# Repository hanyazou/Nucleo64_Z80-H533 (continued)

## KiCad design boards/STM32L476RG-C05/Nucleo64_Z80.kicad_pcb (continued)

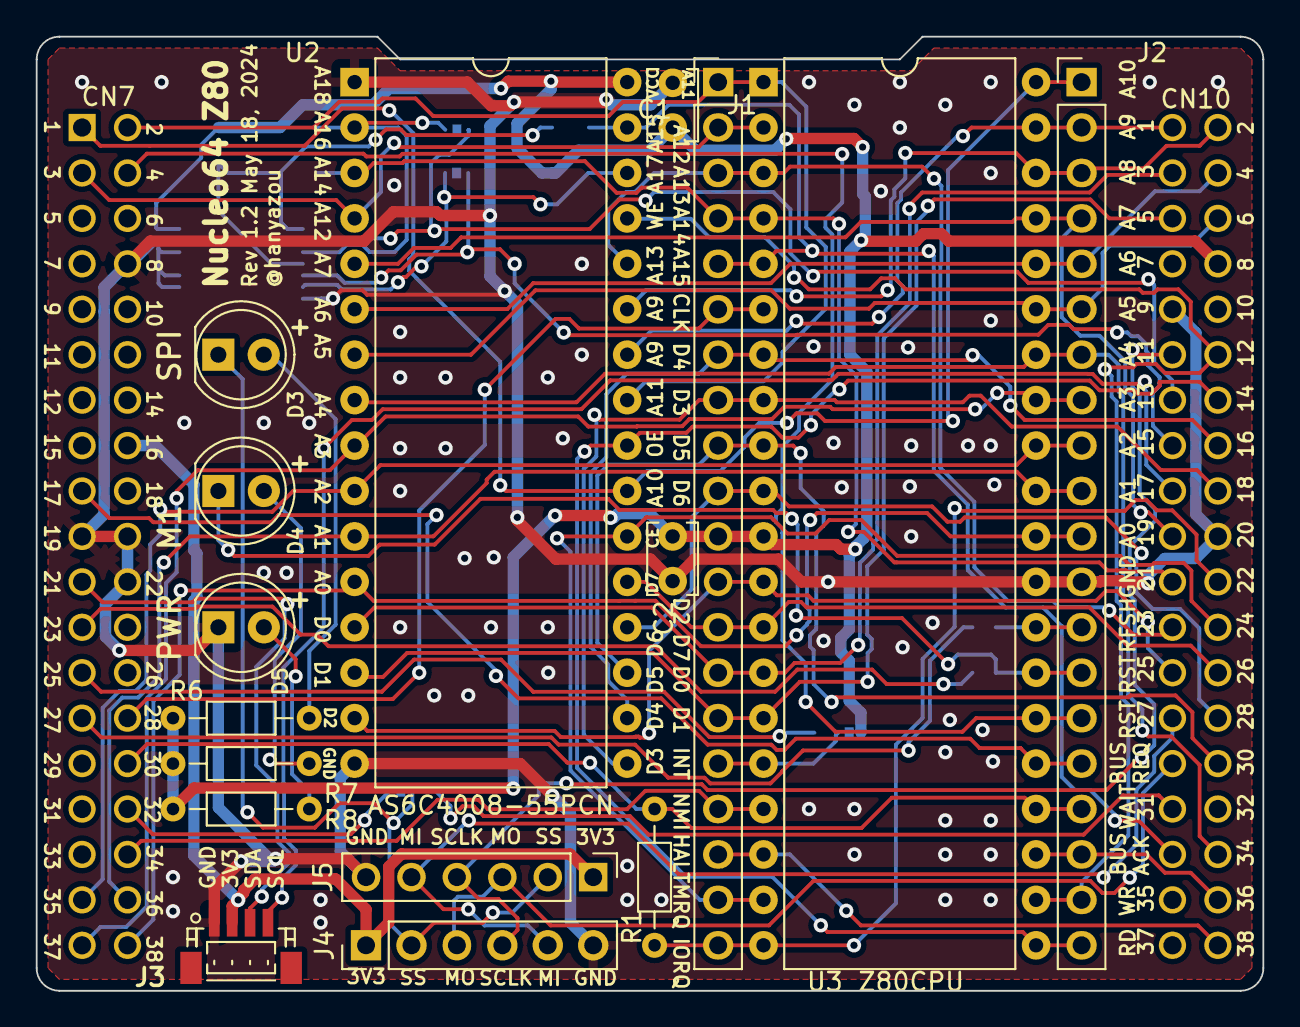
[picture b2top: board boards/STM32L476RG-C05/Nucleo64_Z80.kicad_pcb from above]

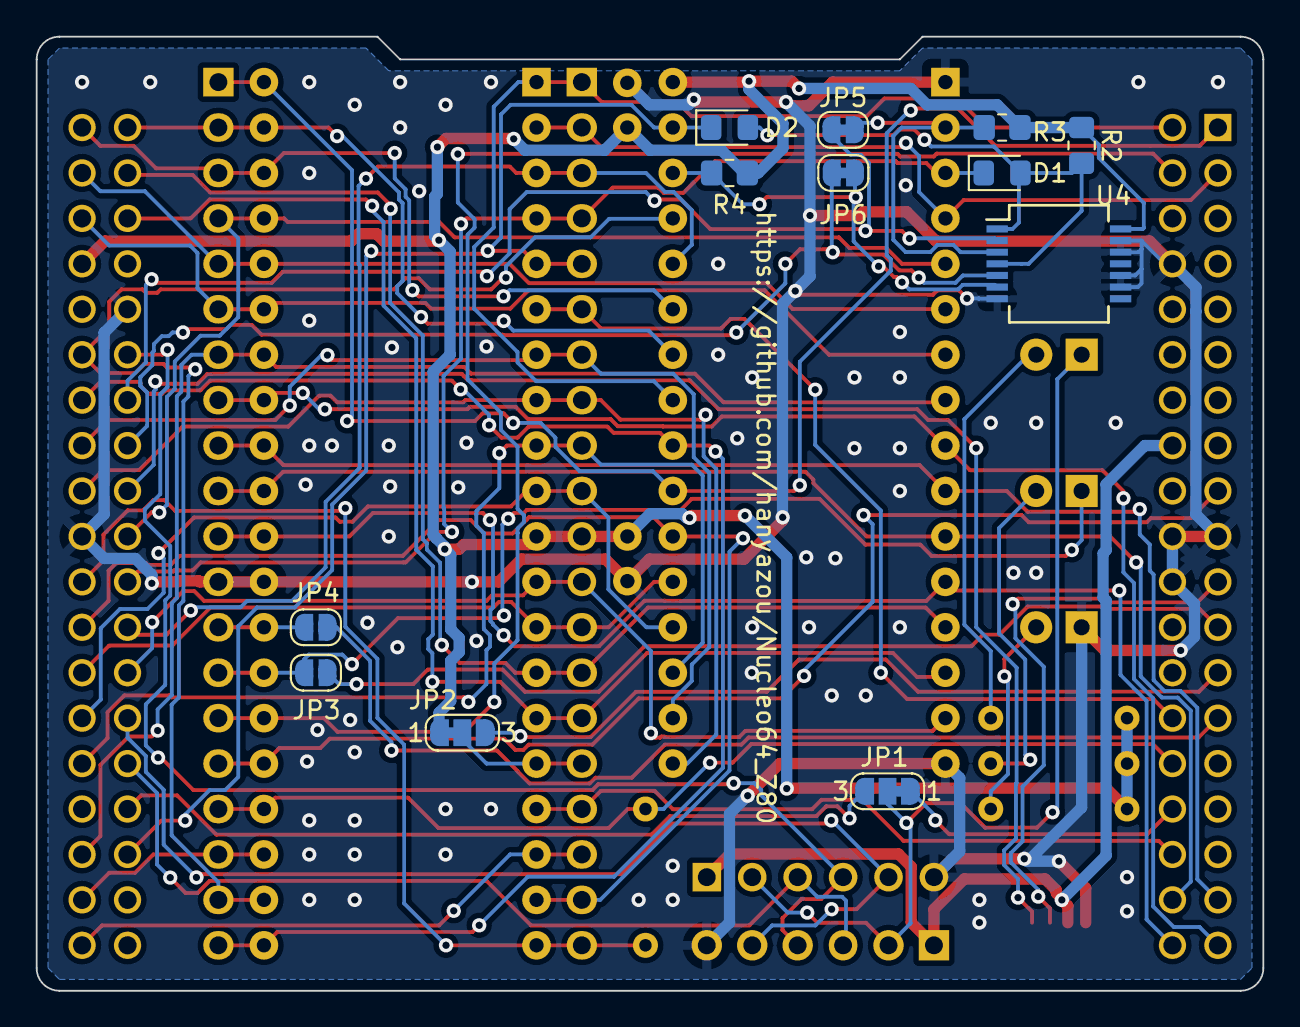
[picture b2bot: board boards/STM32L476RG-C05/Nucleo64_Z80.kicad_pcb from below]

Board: 2 copper layers, 68.6 x 53.3 mm, 29 parts (12 on the bottom side), 60 nets.

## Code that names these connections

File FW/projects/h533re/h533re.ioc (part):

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Mcu.Name=STM32H533RETx
Mcu.Package=LQFP64
Mcu.UserName=STM32H533RETx
PA0.Signal=S_TIM2_CH1
PA1.GPIOParameters=GPIO_Label
PA1.GPIO_Label=Z80_IOREQ
PA1.Signal=GPIO_Input
PA10.GPIOParameters=GPIO_Label
PA10.GPIO_Label=Z80_PWR_EN
PA10.Signal=GPIO_Output
PA11.Mode=Host
PA11.Signal=USB_DM
PA12.Mode=Host
PA12.Signal=USB_DP
PA15(JTDI).GPIOParameters=GPIO_Label
PA15(JTDI).GPIO_Label=Z80_NMI
PA15(JTDI).Signal=GPIO_Input
PA2.Mode=Asynchronous
PA2.Signal=USART2_TX
PA3.Mode=Asynchronous
PA3.Signal=USART2_RX
PA4.GPIOParameters=GPIO_Label
PA4.GPIO_Label=USB_FS_PWR_EN
PA4.Signal=GPIO_Output
PA5.GPIOParameters=GPIO_Label
PA5.GPIO_Label=BANK_SEL0
PA5.Mode=Full_Duplex_Master
PA5.Signal=SPI1_SCK
PA6.GPIOParameters=GPIO_Label
PA6.GPIO_Label=BANK_SEL1
PA6.Mode=Full_Duplex_Master
PA6.Signal=SPI1_MISO
PA7.GPIOParameters=GPIO_Label
PA7.GPIO_Label=Z80_INT
PA7.Mode=Full_Duplex_Master
PA7.Signal=SPI1_MOSI
PA8.GPIOParameters=GPIO_Label
PA8.GPIO_Label=Z80_WAIT
PA8.Signal=GPIO_Input
PA9.GPIOParameters=PinState,GPIO_Label
PA9.GPIO_Label=SPI_SS
PA9.PinState=GPIO_PIN_SET
PA9.Signal=GPIO_Output
PB0.GPIOParameters=GPIO_Label
PB0.GPIO_Label=Z80_D0
PB0.Signal=GPIO_Input
PB1.GPIOParameters=GPIO_Label
PB1.GPIO_Label=Z80_D1
PB1.Signal=GPIO_Input
PB10.Mode=I2C
PB10.Signal=I2C2_SCL
PB12.Mode=I2C
PB12.Signal=I2C2_SDA
PB13.GPIOParameters=GPIO_Label
PB13.GPIO_Label=Z80_A13
PB13.Signal=GPIO_Input
PB14.GPIOParameters=GPIO_Label
PB14.GPIO_Label=Z80_A14
PB14.Signal=GPIO_Input
PB15.GPIOParameters=GPIO_Label
PB15.GPIO_Label=Z80_A15
PB15.Signal=GPIO_Input
PB2.GPIOParameters=GPIO_Label
PB2.GPIO_Label=Z80_D2
PB2.Signal=GPIO_Input
PB3(JTDO/TRACESWO).GPIOParameters=GPIO_Label
PB3(JTDO/TRACESWO).GPIO_Label=Z80_D3
PB3(JTDO/TRACESWO).Signal=GPIO_Input
PB4(NJTRST).GPIOParameters=GPIO_Label
PB4(NJTRST).GPIO_Label=Z80_D4
PB4(NJTRST).Signal=GPIO_Input
PB5.GPIOParameters=GPIO_Label
PB5.GPIO_Label=Z80_D5
PB5.Signal=GPIO_Input
PB6.GPIOParameters=GPIO_Label
PB6.GPIO_Label=Z80_D6
PB6.Signal=GPIO_Input
PB7.GPIOParameters=GPIO_Label
PB7.GPIO_Label=Z80_D7
PB7.Signal=GPIO_Input
PB8.GPIOParameters=GPIO_Label
PB8.GPIO_Label=Z80_RD
PB8.Signal=GPIO_Input
PC0.GPIOParameters=GPIO_Label
PC0.GPIO_Label=Z80_A0
PC0.Signal=GPIO_Input
PC1.GPIOParameters=GPIO_Label
PC1.GPIO_Label=Z80_A1
PC1.Signal=GPIO_Input
PC10.GPIOParameters=GPIO_Label
PC10.GPIO_Label=Z80_A10
PC10.Signal=GPIO_Input
PC11.GPIOParameters=GPIO_Label
PC11.GPIO_Label=Z80_A11
PC11.Signal=GPIO_Input
PC12.GPIOParameters=GPIO_Label
PC12.GPIO_Label=Z80_A12
PC12.Signal=GPIO_Input
PC13.GPIOParameters=GPIO_Label
PC13.GPIO_Label=Z80_RESET
PC13.Signal=GPIO_Input
PC14-OSC32_IN(OSC32_IN).GPIOParameters=GPIO_Label
PC14-OSC32_IN(OSC32_IN).GPIO_Label=Z80_MEMRQ
PC14-OSC32_IN(OSC32_IN).Signal=GPIO_Input
PC15-OSC32_OUT(OSC32_OUT).GPIOParameters=GPIO_Label
PC15-OSC32_OUT(OSC32_OUT).GPIO_Label=Z80_WR
PC15-OSC32_OUT(OSC32_OUT).Signal=GPIO_Input
PC2.GPIOParameters=GPIO_Label
PC2.GPIO_Label=Z80_A2
PC2.Signal=GPIO_Input
PC3.GPIOParameters=GPIO_Label
PC3.GPIO_Label=Z80_A3
PC3.Signal=GPIO_Input
PC4.GPIOParameters=GPIO_Label
PC4.GPIO_Label=Z80_A4
PC4.Signal=GPIO_Input
PC5.GPIOParameters=GPIO_Label
PC5.GPIO_Label=Z80_A5
PC5.Signal=GPIO_Input
PC6.GPIOParameters=GPIO_Label
PC6.GPIO_Label=Z80_A6
PC6.Signal=GPIO_Input
PC7.GPIOParameters=GPIO_Label
PC7.GPIO_Label=Z80_A7
PC7.Signal=GPIO_Input
PC8.GPIOParameters=GPIO_Label
PC8.GPIO_Label=Z80_A8
PC8.Signal=GPIO_Input
PC9.GPIOParameters=GPIO_Label
PC9.GPIO_Label=Z80_A9
PC9.Signal=GPIO_Input
PD2.GPIOParameters=GPIO_Label
PD2.GPIO_Label=Z80_BUSRQ
PD2.Signal=GPIO_Input
RCC.HSE_VALUE=25000000
RCC.SYSCLKFreq_VALUE=248000000
RCC.SYSCLKSource=RCC_SYSCLKSOURCE_PLLCLK
board=custom

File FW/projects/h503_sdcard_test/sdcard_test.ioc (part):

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Mcu.Name=STM32L476R(C-E-G)Tx
Mcu.Package=LQFP64
Mcu.UserName=STM32L476RGTx
PA0.Signal=S_TIM5_CH1
PA1.GPIOParameters=GPIO_PuPd,GPIO_Label
PA1.GPIO_Label=Z80_WAIT
PA1.GPIO_PuPd=GPIO_PULLUP
PA1.Signal=GPIO_Input
PA10.GPIOParameters=GPIO_PuPd,GPIO_Label
PA10.GPIO_Label=Z80_A15
PA10.GPIO_PuPd=GPIO_NOPULL
PA10.Signal=GPIO_Input
PA11.GPIOParameters=GPIO_PuPd,GPIO_Label
PA11.GPIO_Label=Z80_RD
PA11.GPIO_PuPd=GPIO_PULLUP
PA11.Signal=GPIO_Input
PA12.GPIOParameters=GPIO_PuPd,GPIO_Label
PA12.GPIO_Label=Z80_WR
PA12.GPIO_PuPd=GPIO_PULLUP
PA12.Signal=GPIO_Input
PA13\ (JTMS-SWDIO).GPIOParameters=GPIO_Label
PA13\ (JTMS-SWDIO).GPIO_Label=TMS
PA13\ (JTMS-SWDIO).Mode=Serial_Wire
PA13\ (JTMS-SWDIO).Signal=SYS_JTMS-SWDIO
PA14\ (JTCK-SWCLK).GPIOParameters=GPIO_Label
PA14\ (JTCK-SWCLK).GPIO_Label=TCK
PA14\ (JTCK-SWCLK).Mode=Serial_Wire
PA14\ (JTCK-SWCLK).Signal=SYS_JTCK-SWCLK
PA15\ (JTDI).GPIOParameters=GPIO_Label
PA15\ (JTDI).GPIO_Label=Z80_BUSRQ
PA15\ (JTDI).Signal=GPIO_Output
PA2.GPIOParameters=GPIO_Speed,GPIO_PuPd,GPIO_Label,GPIO_Mode
PA2.GPIO_Label=USART_TX
PA2.GPIO_Mode=GPIO_MODE_AF_PP
PA2.GPIO_PuPd=GPIO_NOPULL
PA2.GPIO_Speed=GPIO_SPEED_FREQ_VERY_HIGH
PA2.Mode=Asynchronous
PA2.Signal=USART2_TX
PA3.GPIOParameters=GPIO_Speed,GPIO_PuPd,GPIO_Label,GPIO_Mode
PA3.GPIO_Label=USART_RX
PA3.GPIO_Mode=GPIO_MODE_AF_PP
PA3.GPIO_PuPd=GPIO_NOPULL
PA3.GPIO_Speed=GPIO_SPEED_FREQ_VERY_HIGH
PA3.Mode=Asynchronous
PA3.Signal=USART2_RX
PA4.GPIOParameters=PinState,GPIO_Label
PA4.GPIO_Label=SPI1_SS
PA4.PinState=GPIO_PIN_SET
PA4.Signal=GPIO_Output
PA5.Mode=Full_Duplex_Master
PA5.Signal=SPI1_SCK
PA6.GPIOParameters=GPIO_Label
PA6.GPIO_Label=BANK_SEL0
PA6.Signal=GPIO_Output
PA7.GPIOParameters=GPIO_Label
PA7.GPIO_Label=BANK_SEL1
PA7.Signal=GPIO_Output
PA8.GPIOParameters=GPIO_Label
PA8.GPIO_Label=Z80_A13
PA8.Signal=GPIO_Input
PA9.GPIOParameters=GPIO_Label
PA9.GPIO_Label=Z80_A14
PA9.Signal=GPIO_Input
PB0.GPIOParameters=GPIO_Label
PB0.GPIO_Label=Z80_NMI
PB0.Signal=GPIO_Output
PB1.GPIOParameters=GPIO_PuPd,GPIO_Label
PB1.GPIO_Label=Z80_MEMRQ
PB1.GPIO_PuPd=GPIO_PULLUP
PB1.Signal=GPIO_Input
PB10.Signal=GPIO_Input
PB11.Signal=GPIO_Input
PB12.Signal=GPIO_Input
PB13.Signal=GPIO_Input
PB14.Signal=GPIO_Input
PB15.Signal=GPIO_Input
PB2.GPIOParameters=GPIO_PuPd,GPIO_Label
PB2.GPIO_Label=Z80_IOREQ
PB2.GPIO_PuPd=GPIO_PULLUP
PB2.Signal=GPIO_Input
PB4\ (NJTRST).Mode=Full_Duplex_Master
PB4\ (NJTRST).Signal=SPI1_MISO
PB5.Mode=Full_Duplex_Master
PB5.Signal=SPI1_MOSI
PB6.Mode=I2C
PB6.Signal=I2C1_SCL
PB7.Mode=I2C
PB7.Signal=I2C1_SDA
PB8.Signal=GPIO_Input
PB9.Signal=GPIO_Input
PC0.Signal=GPIO_Input
PC1.Signal=GPIO_Input
PC10.Signal=GPIO_Input
PC11.Signal=GPIO_Input
PC12.Signal=GPIO_Input
PC2.Signal=GPIO_Input
PC3.Signal=GPIO_Input
PC4.Signal=GPIO_Input
PC5.Signal=GPIO_Input
PC6.Signal=GPIO_Input
PC7.Signal=GPIO_Input
PC8.Signal=GPIO_Input
PC9.Signal=GPIO_Input
PD2.GPIOParameters=GPIO_Label
PD2.GPIO_Label=Z80_RESET
PD2.Signal=GPIO_Output
PH0-OSC_IN\ (PH0).Signal=RCC_OSC_IN
PH1-OSC_OUT\ (PH1).Signal=RCC_OSC_OUT
RCC.HSE_VALUE=8000000
RCC.SYSCLKFreq_VALUE=80000000
RCC.SYSCLKSource=RCC_SYSCLKSOURCE_PLLCLK
board=NUCLEO-L476RG
boardIOC=true

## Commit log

2026-01-03 boards: Rename kicad to STM32L476RG-C05
2026-01-04 boards: Add STM32H533RE-C02 (copy of STM32L476RG-C05)
2026-01-05 stm32h533re: Fix schematics
2026-01-05 stm32h533re: Fix PCB layout
2026-01-05 stm32h533re: Add gerber archive Nucleo64_Z80-2.0.zip
2026-01-11 fw: Create new project h533_usb_host_test
2026-01-11 fw: h533_usb_host_test: Enable USART2 as the debug serial
2026-01-11 fw: h533_usb_host_test: Enable 1-way ICACHE
2026-01-11 fw: h533_usb_host_test: Add USB host and GPIO USB_FS_PWR_EN
2026-01-31 fw: h533_usb_host_test: Add FileX, ThreadX and USBX
2026-01-31 fw: h533_usb_host_test: Use TIM1 for the Timebase Source
2026-01-31 fw: h533_usb_host_test: Fix USBX configuration parameters
2026-01-31 fw: h533_usb_host_test: Display USBX events adn errors
2026-01-31 fw: h533_usb_host_test: Call ux_host_stack_hcd_register() and HAL_HCD_Start()
2026-01-31 fw: h533_usb_host_test: Add msc_test and read floppy disk sectors with READ(10)
2026-01-31 fw: Add .cproject files
2026-02-07 fw: h533re: Regenerate code after updating CubeMX configuration
2026-02-07 fw: Create new project h533re
2026-02-07 tools: zasm: Ignore dirty state of zasm submodule on case-insensitive filesystems
    The zasm submodule contains files that differ only by case (e.g. Hello.asm vs hello.asm),
    which shows up as modified on macOS default case-insensitive filesystems.
    Set submodule ignore=dirty to keep git status clean.
2026-02-07 fw: h533re: Configure system clock and peripherals for board bring-up
    * USART2
    115200 8N1
    NVIC enable global interrupt
    GPIO PA2 USART2 TX
    GPIO PA3 USART2 RX
    * System Core
2026-02-07 fw: h533re: Add libraries imported by CubeMX
2026-02-08 fw: h533re: Enable printf() using USART2 debug serial
2026-02-08 fw: h533re: Call ux_host_stack_hcd_register() and HAL_HCD_Start()
2026-02-08 fw: h533re: Fix USBX configuration parameters
2026-02-08 fw: h533re: Display USBX events and errors
2026-02-08 fw: nucleo64_z80: Add main routine and msc
2026-02-08 fw: nucleo64_z80: Add main thread to call nucleo64_z80 main routine
2026-02-08 fw: nucleo64_z80: Add util: delay_us(), input_key_available() and getchar()
2026-02-08 fw: nucleo64_z80: Fix z80
2026-02-08 fw: nucleo64_z80: Add z80_io and ipl (ipl is not used yet)
2026-02-08 fw: nucleo64_z80: Add z80 (copy of board_test)
2026-02-15 fw: nucleo64_z80: uart: Fix getchar() blocking by making _read() wait for RX data
2026-02-15 fw: h533re: Call sd_spi_start() to allow SPI pins to be shared with GPIO
2026-02-15 fw: nucleo64_z80: Add detailed comments for Z80 I/O bus control and refactor (no functional change)
2026-02-15 fw: nucleo64_z80: Add sd_spi_start(), sd_spi_acquire() and sd_spi_release()
2026-02-15 fw: nucleo64_z80: Import FatFs from STM32L476 sdcard_test project as-is
2026-02-15 fw: nucleo64_z80: Add mem_init() to probe Z80 RAM and verify bank mapping
2026-02-15 fw: h533re: Enable SPI for GPIO-shared pins (additional setup required) (fixed)
2026-02-15 fw: h533re: Add /fatfs path to CubeIDE project configuration
2026-02-15 fw: nucleo64_z80: Separate UART-related code from util.c into uart.c
2026-02-15 fw: nucleo64_z80: Fix FatFs to compile with nucleo64_z80
2026-02-15 fw: h533re: Enable SPI for GPIO-shared pins (additional setup required)
2026-02-15 fw: nucleo64_z80: Change Z80 pin init/deinit API to acquire/release with saved state
2026-02-21 fw: nucleo64_z80: Add sd_disk()
2026-02-21 fw: nucleo64_z80: Fix z80_release_pins() to keep driving essential pins
2026-02-21 fw: nucleo64_z80: Add mmu_bank_*() prototype to z80.h
2026-02-21 fw: nucleo64_z80: Change UART_CREG value to Z80-Simulator style
2026-02-21 fw: nucleo64_z80: Rename mem_store...() and mem_load...() to mem_write() and mem_read()
2026-02-21 fw: nucleo64_z80: Fix z80_io to boot CP/M
2026-02-21 fw: nucleo64_z80: Change message new line code to '\r\n'
2026-02-21 fw: nucleo64_z80: Add disk_drive
2026-02-21 fw: nucleo64_z80: Initialize Z80 INT/NMI pins to inactive to prevent spurious interrupts
2026-02-23 fw: nucleo64_z80: Add USB MSC disk
2026-02-23 fw: nucleo64_z80: Silence non-error USB/SCSI messages
2026-03-20 Move old STM32 projects into projects folder
